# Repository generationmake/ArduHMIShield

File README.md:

# ArduHMIShield
ArduHMIShield with EA DOGM graphic display and joystick compatible to Arduino Uno

### Holder

The holder is constructed using FreeCAD. It is 3D-printable. The files are in the folder `production-data`

## PCB

### Top

### Bottom

### Order options

The pcb is available at Aisler: https://aisler.net/p/FNAGFCPP

## License

This hardware is licensed under the CERN OHL v. 1.2

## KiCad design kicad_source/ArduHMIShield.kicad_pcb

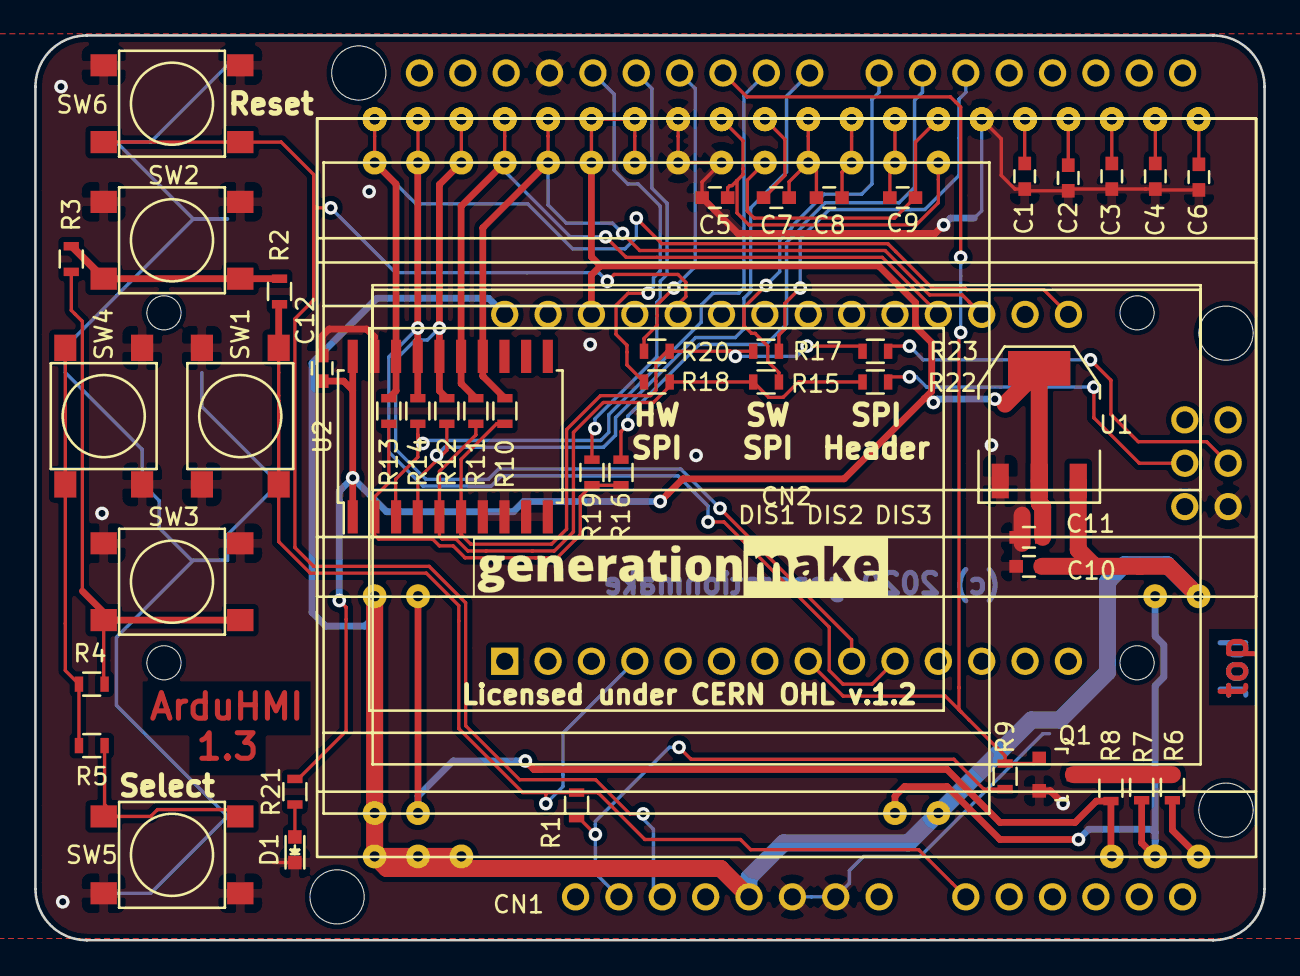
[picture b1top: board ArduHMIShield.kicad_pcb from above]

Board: 2 copper layers, 72.0 x 53.0 mm, 52 parts (1 on the bottom side), 45 nets.

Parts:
C1, C2, C3, C4, C5, C6, C7, C8, C9, C10, C11: 1uF; C_0603
C12: 100nF; C_0603
CN1: ARDUINO_ISP; ARDUINO_ISP_TOP
CN2: ARDUINO_MKR; ARDUINO_MKR_HOLES
D1: 150060GS75000; LED_0603
DIS1: EA_DOGM128-6; EA_DOGM128
DIS2: EA_DOGM132-5; EA_DOGM081_162_163_132
DIS3: EA_DOGS102-6; EA_DOGS102
L1, L2: Label; generationmake_logo
Q1: 2N7002; SOT-23
R1: 2k; R_0603
R2: 330; R_0603
R3: 620; R_0603
R4, R9, R21: 1k; R_0603
R5: 3k3; R_0603
R6, R7, R8: 30; R_0603
R10, R11, R12, R13, R14, R15, R17, R19, R22, R23: DNI; R_0603
R16, R18, R20: 0R; R_0603
SW1, SW2, SW3, SW4, SW5: TAST_VER; WE_430182080816
SW6: TAST_VER; WE_430182050816
U1: AZ1117IH-3.3; SOT-223
U2: 74VHC245D; SOIC-20_7.5x12.8mm_Pitch1.27mm

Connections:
+3V3: C11.1, C12.1, CN2.26, DIS1.34, DIS1.35, DIS2.34, DIS2.35, DIS3.22, DIS3.23, R21.2, U1.2, U1.4, U2.1, U2.20
+5V: C10.1, CN1.27, CN2.28, DIS1.1, DIS1.2, DIS1.3, DIS2.1, DIS2.20, DIS3.1, DIS3.14, U1.3
/ARDU_A0: CN1.8, R12.2, U2.4
/ARDU_CLK: R11.2, R15.2, R18.2, R22.2, U2.5
/ARDU_CLK_1: CN1.13, R18.1
/ARDU_CLK_2: CN1.7, R15.1
/ARDU_CLK_3: CN1.43, R22.1
/ARDU_CS: R13.2, R16.2, R19.2, U2.2
/ARDU_CS_1: CN1.12, R19.1
/ARDU_CS_2: CN1.6, R16.1
/ARDU_RESET: CN1.9, R14.2, U2.3
/ARDU_SI: R10.2, R17.2, R20.2, R23.2, U2.6
/ARDU_SI_1: CN1.11, R20.1
/ARDU_SI_2: CN1.5, R17.1
/ARDU_SI_3: CN1.44, R23.1
/BUTTON_DOWN: R3.2, R4.1, SW3.2, SW3.4
/BUTTON_LEFT: R4.2, R5.1, SW4.2, SW4.4
/BUTTON_SELECT: R5.2, SW5.2, SW5.4
/BUTTON_UP: R2.2, R3.1, SW2.2, SW2.4
/DISPLAY_BL: CN1.10, CN2.8, Q1.1, R9.2
/DIS_A0: CN2.9, DIS1.38, DIS2.38, DIS3.26, R12.1, U2.16
/DIS_C1: DIS1.18, DIS2.2, DIS3.2, R8.1
/DIS_C2: DIS1.19, DIS2.19, DIS3.13, R7.1
/DIS_C3: DIS1.20, R6.1
/DIS_CAP1N: C7.2, C8.1, DIS1.30, DIS2.30, DIS3.18
/DIS_CAP1P: C8.2, DIS1.29, DIS2.29, DIS3.17
/DIS_CAP2N: C9.2, DIS1.27, DIS2.27, DIS3.19
/DIS_CAP2P: C9.1, DIS1.28, DIS2.28, DIS3.16
/DIS_CAP3P: C7.1, DIS1.31, DIS2.31
/DIS_CLK: CN2.18, DIS1.37, DIS2.37, DIS3.25, R11.1, U2.15
/DIS_CS: CN2.15, DIS1.40, DIS2.40, DIS3.28, R13.1, U2.18
/DIS_RESET: CN2.10, DIS1.39, DIS2.39, DIS3.27, R14.1, U2.17
/DIS_SI: CN2.17, DIS1.36, DIS2.36, DIS3.24, R10.1, U2.14
/DIS_V0: C6.1, DIS1.21, DIS2.21
/DIS_V1: C4.1, DIS1.22, DIS2.22
/DIS_V2: C3.1, DIS1.23, DIS2.23
/DIS_V3: C2.1, DIS1.24, DIS2.24
/DIS_V4: C1.1, DIS1.25, DIS2.25
/DIS_VOUT: C5.1, DIS1.32, DIS2.32, DIS3.15
/KEYPAD_A0: CN1.23, CN2.4, R1.2, R2.1, SW1.2, SW1.4
/RESET: CN1.29, CN2.24, SW6.2, SW6.4
GND: C1.2, C2.2, C3.2, C4.2, C5.2, C6.2, C10.2, C11.2, C12.2, CN1.14, CN1.25, CN1.26, CN1.46, CN2.25, D1.1, DIS1.26, DIS1.33, DIS2.26, DIS2.33, DIS3.20, DIS3.21, Q1.2, SW1.1, SW1.3, SW2.1, SW2.3, SW3.1, SW3.3, SW4.1, SW4.3, SW5.1, SW5.3, SW6.1, SW6.3, U1.1, U2.7, U2.8, U2.9, U2.10, U2.19
unnamed: D1.2, R21.1
unnamed: Q1.3, R6.2, R7.2, R8.2
VIO: CN1.30, R1.1, R9.1

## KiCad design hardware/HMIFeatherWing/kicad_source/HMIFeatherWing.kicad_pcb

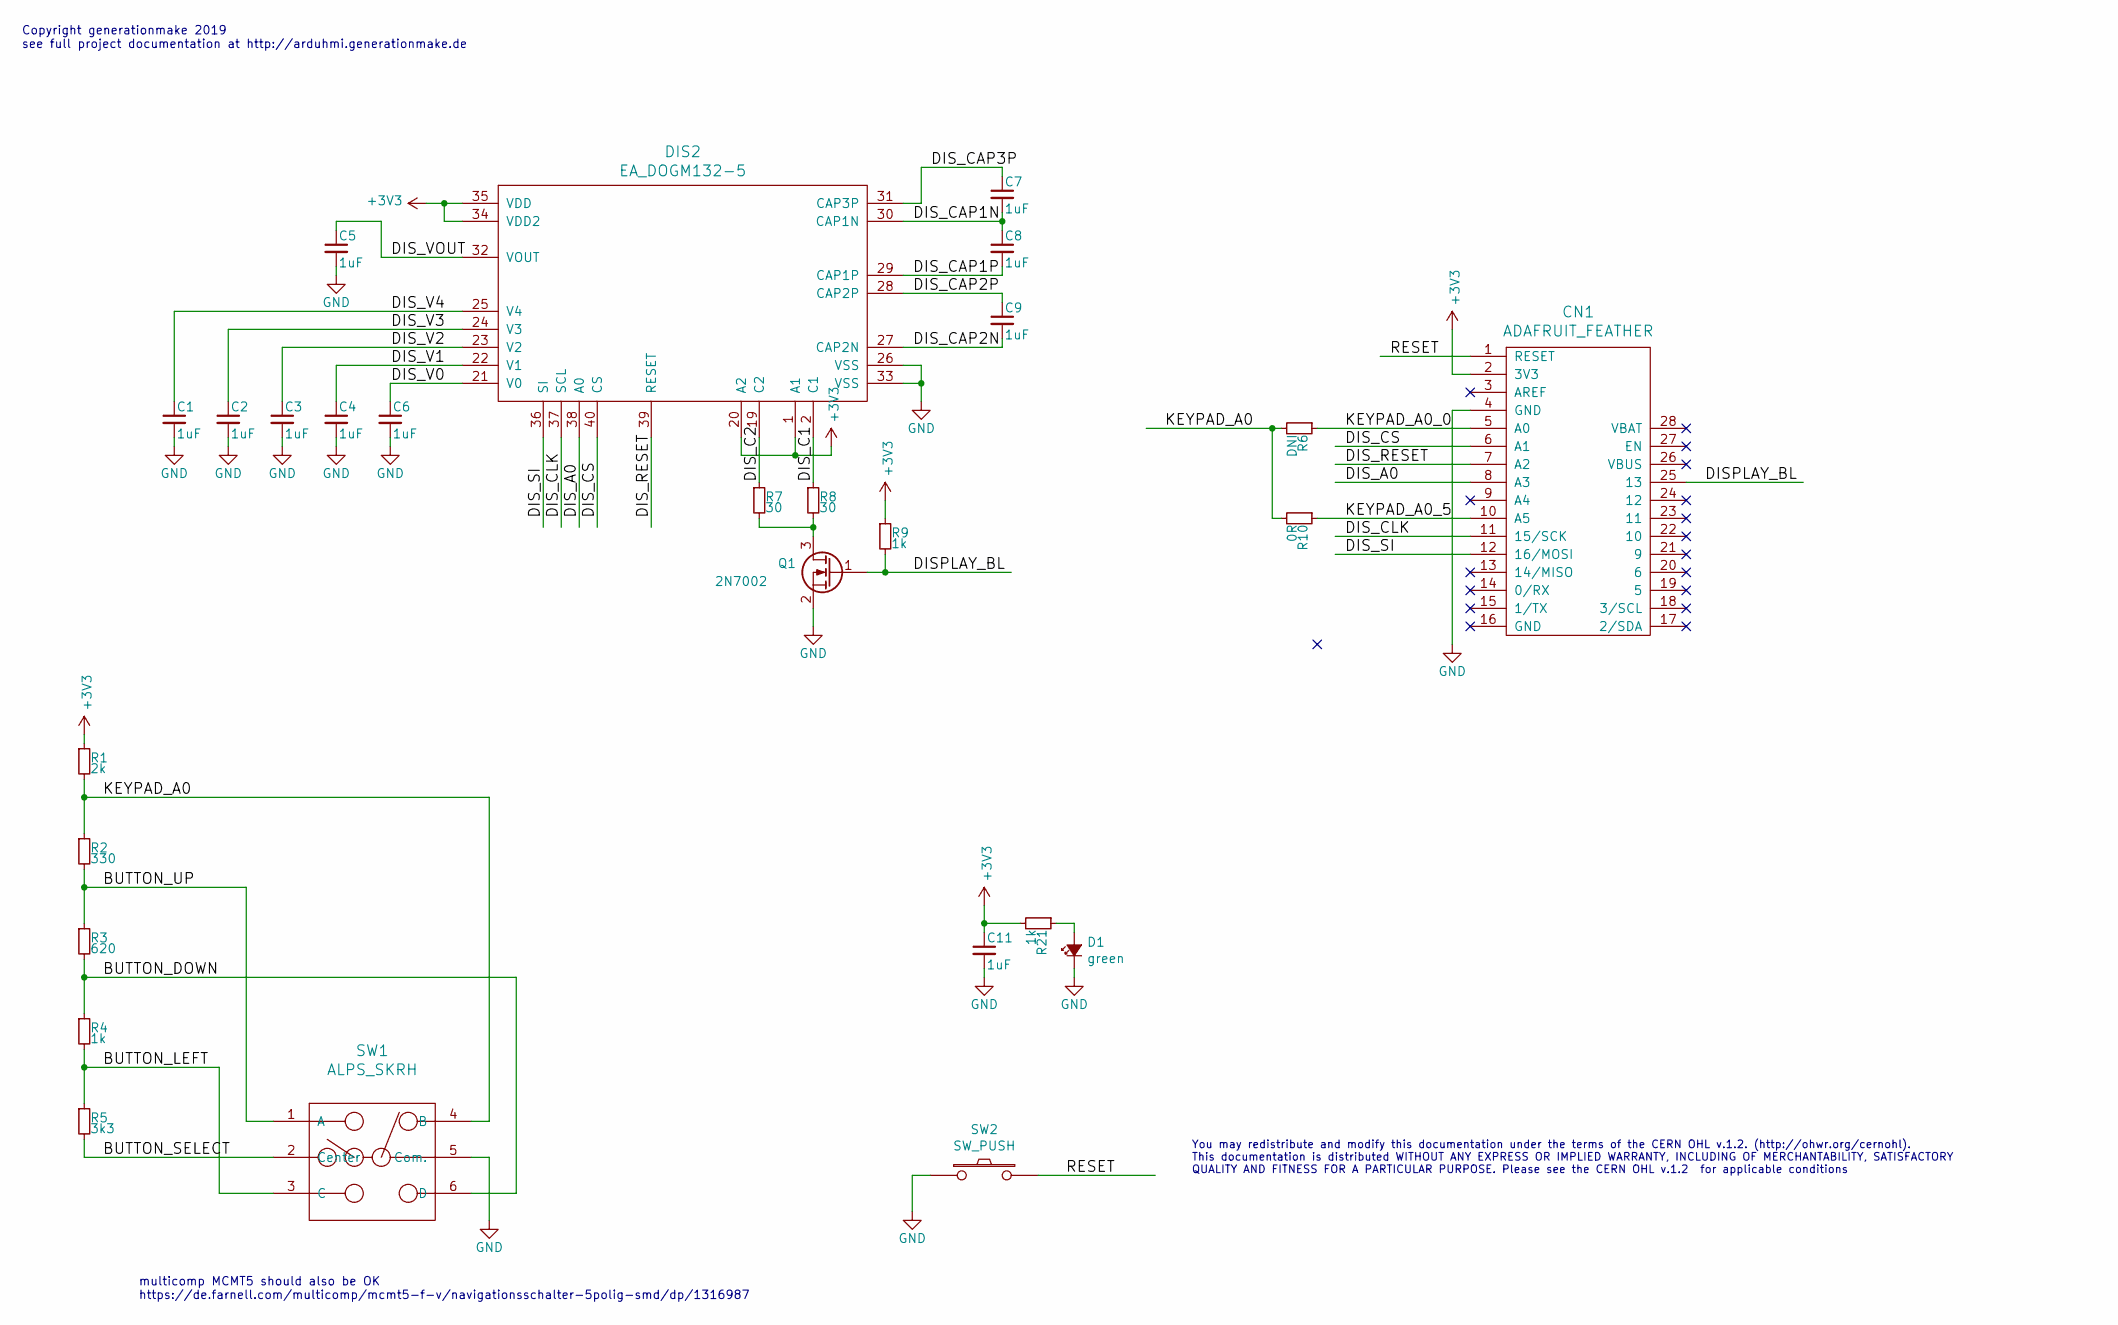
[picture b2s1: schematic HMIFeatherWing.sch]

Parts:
C1, C2, C3, C4, C5, C6, C7, C8, C9, C11: 1uF; C_0603
CN1: ADAFRUIT_FEATHER; ADAFRUIT_FEATHER_HOLES
D1: green; LED_0603
DIS2: EA_DOGM132-5; EA_DOGM081_162_163_132
Q1: 2N7002; SOT-23
R1: 2k; R_0603
R2: 330; R_0603
R3: 620; R_0603
R4, R9, R21: 1k; R_0603
R5: 3k3; R_0603
R6: DNI; R_0603
R7, R8: 30; R_0603
R10: 0R; R_0603
SW1: ALPS_SKRH
SW2: SW_PUSH; smd_push

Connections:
+3V3: C11.1, CN1.2 (3V3), DIS2.1 (A1), DIS2.20 (A2), DIS2.34 (VDD2), DIS2.35 (VDD), R1.1, R9.1, R21.2
/BUTTON_DOWN: R3.2, R4.1, SW1.6 (D)
/BUTTON_LEFT: R4.2, R5.1, SW1.3 (C)
/BUTTON_SELECT: R5.2, SW1.2 (Center)
/BUTTON_UP: R2.2, R3.1, SW1.1 (A)
/DISPLAY_BL: CN1.25 (13), Q1.1 (G), R9.2
/DIS_A0: CN1.8 (A3), DIS2.38 (A0)
/DIS_C1: DIS2.2 (C1), R8.1
/DIS_C2: DIS2.19 (C2), R7.1
/DIS_CAP1N: C7.2, C8.1, DIS2.30 (CAP1N)
/DIS_CAP1P: C8.2, DIS2.29 (CAP1P)
/DIS_CAP2N: C9.2, DIS2.27 (CAP2N)
/DIS_CAP2P: C9.1, DIS2.28 (CAP2P)
/DIS_CAP3P: C7.1, DIS2.31 (CAP3P)
/DIS_CLK: CN1.11 (15/SCK), DIS2.37 (SCL)
/DIS_CS: CN1.6 (A1), DIS2.40 (CS)
/DIS_RESET: CN1.7 (A2), DIS2.39 (RESET)
/DIS_SI: CN1.12 (16/MOSI), DIS2.36 (SI)
/DIS_V0: C6.1, DIS2.21 (V0)
/DIS_V1: C4.1, DIS2.22 (V1)
/DIS_V2: C3.1, DIS2.23 (V2)
/DIS_V3: C2.1, DIS2.24 (V3)
/DIS_V4: C1.1, DIS2.25 (V4)
/DIS_VOUT: C5.1, DIS2.32 (VOUT)
/KEYPAD_A0: R1.2, R2.1, R6.2, R10.2, SW1.4 (B)
/KEYPAD_A0_0: CN1.5 (A0), R6.1
/KEYPAD_A0_5: CN1.10 (A5), R10.1
/RESET: CN1.1 (RESET), SW2.2
GND: C1.2, C2.2, C3.2, C4.2, C5.2, C6.2, C11.2, CN1.4 (GND), D1.1 (K), DIS2.26 (VSS), DIS2.33 (VSS), Q1.2 (S), SW1.5 (Com.), SW2.1
unnamed: D1.2 (A), R21.1
unnamed: Q1.3 (D), R7.2, R8.2

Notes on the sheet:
Copyright generationmake 2019 see full project documentation at http://arduhmi.generationmake.de
You may redistribute and modify this documentation under the terms of the CERN OHL v.1.2. (http://ohwr.org/cernohl). This documentation is distributed WITHOUT ANY EXPRESS OR IMPLIED WARRANTY, INCLUDING OF MERCHANTABILITY, SATISFACTORY QUALITY AND FITNESS FOR A PARTICULAR PURPOSE. Please see the CER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
multicomp MCMT5 should also be OK https://de.farnell.com/multicomp/mcmt5-f-v/navigationsschalter-5polig-smd/dp/1316987

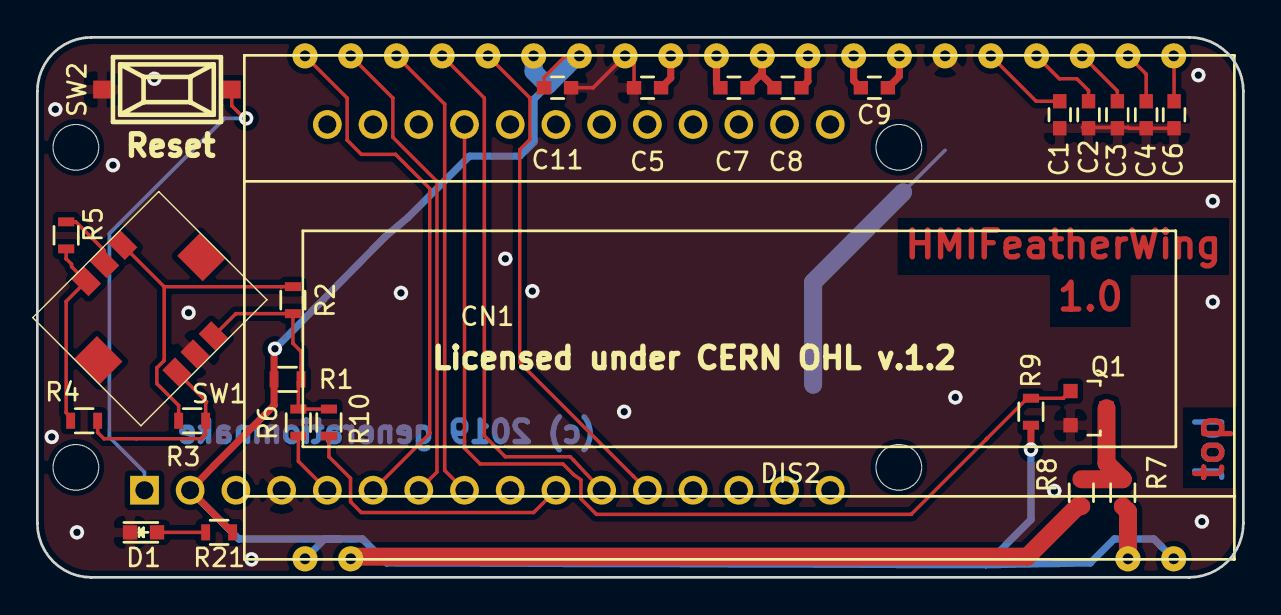
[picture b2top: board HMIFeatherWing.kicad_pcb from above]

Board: 2 copper layers, 67.0 x 30.0 mm, 27 parts (0 on the bottom side), 31 nets.

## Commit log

2018-10-04 added project files
2018-10-04 reworked schematic and layout, both seem to be finished
2018-10-04 generated pdf schematic
2018-10-07 updated schematic and layout
2018-10-08 finished layout and generated output files
2019-03-17 started documentation
2019-06-24 updated documentation
2019-06-24 added gerber for version 1.0
2019-06-24 updated pcb and schematic to version 1.1, see changes in CHANGES.txt
2019-06-24 removed bak files
2019-06-24 generated gerber and pdf files
2019-06-24 added bom
2019-06-24 added zip file with all data for rev 1.1
2019-06-28 completed reichelt BOM, added source code of scrolling badge
2019-06-28 updated BOM with farnell and digikey order numbers
2019-06-29 updated design files to better support Aisler
2019-08-23 removed short cut, corrected silkscreen
2019-08-23 added Arduino SPI header, updated all files
2019-08-23 added zip file with all data
2019-10-19 updated layout to get nicer 3D model
2019-10-20 started sub project MKRHMIShield
2019-10-20 exchanged switches with a joystick
2019-10-21 added 3D body of display
2019-11-19 copied new pcb HMIFeatherWing from MKRHMIShield
2019-11-19 made schematic and layout
2019-12-04 checked pins to fit to other feather wings, used smaller reset, corrected joystick orientation, connected backlight, made board smaller, finished layout
2019-12-04 update title block and generated pdfs
2020-08-19 removed files not belonging to project
2020-08-19 moved files to correct folder
2020-08-19 removed gerber files
2020-08-19 restored intro image
2020-08-19 changed documentation to docs
2020-08-19 added Readme
2020-08-30 added Arduino MKR conector
2020-08-30 updated layout
2020-08-30 added holes for MKR connector
2020-08-30 rounded edge of pcb
2020-08-30 updated order numbers
2020-08-30 generated pdfs, updated changes file
2020-08-30 added images of pcb
2020-08-30 added step file of board
2020-09-12 added link to aisler
2021-02-14 added freecad project for holder
2021-02-14 added production data for holder
2021-02-14 added image of holder and updated readme
2021-02-16 slightly updated holder, made slot for pcb wider
2021-02-17 created and tested display frame
2021-02-17 added step and .gitignore
2021-02-17 .gitignore is now working

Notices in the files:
hardware/HMIFeatherWing/kicad_source/HMIFeatherWing.kicad_pcb:
Licensed under CERN OHL v.1.2
(c) 2019 generationmake
This documentation describes Open Hardware and is licensed
under the CERN OHL v. 1.2.
hardware/HMIFeatherWing/kicad_source/HMIFeatherWing.sch:
This documentation describes Open Hardware and is licensed under the CERN OHL v. 1.2.
kicad_source/ArduHMIShield.kicad_pcb:
(c) 2020 generationmake
